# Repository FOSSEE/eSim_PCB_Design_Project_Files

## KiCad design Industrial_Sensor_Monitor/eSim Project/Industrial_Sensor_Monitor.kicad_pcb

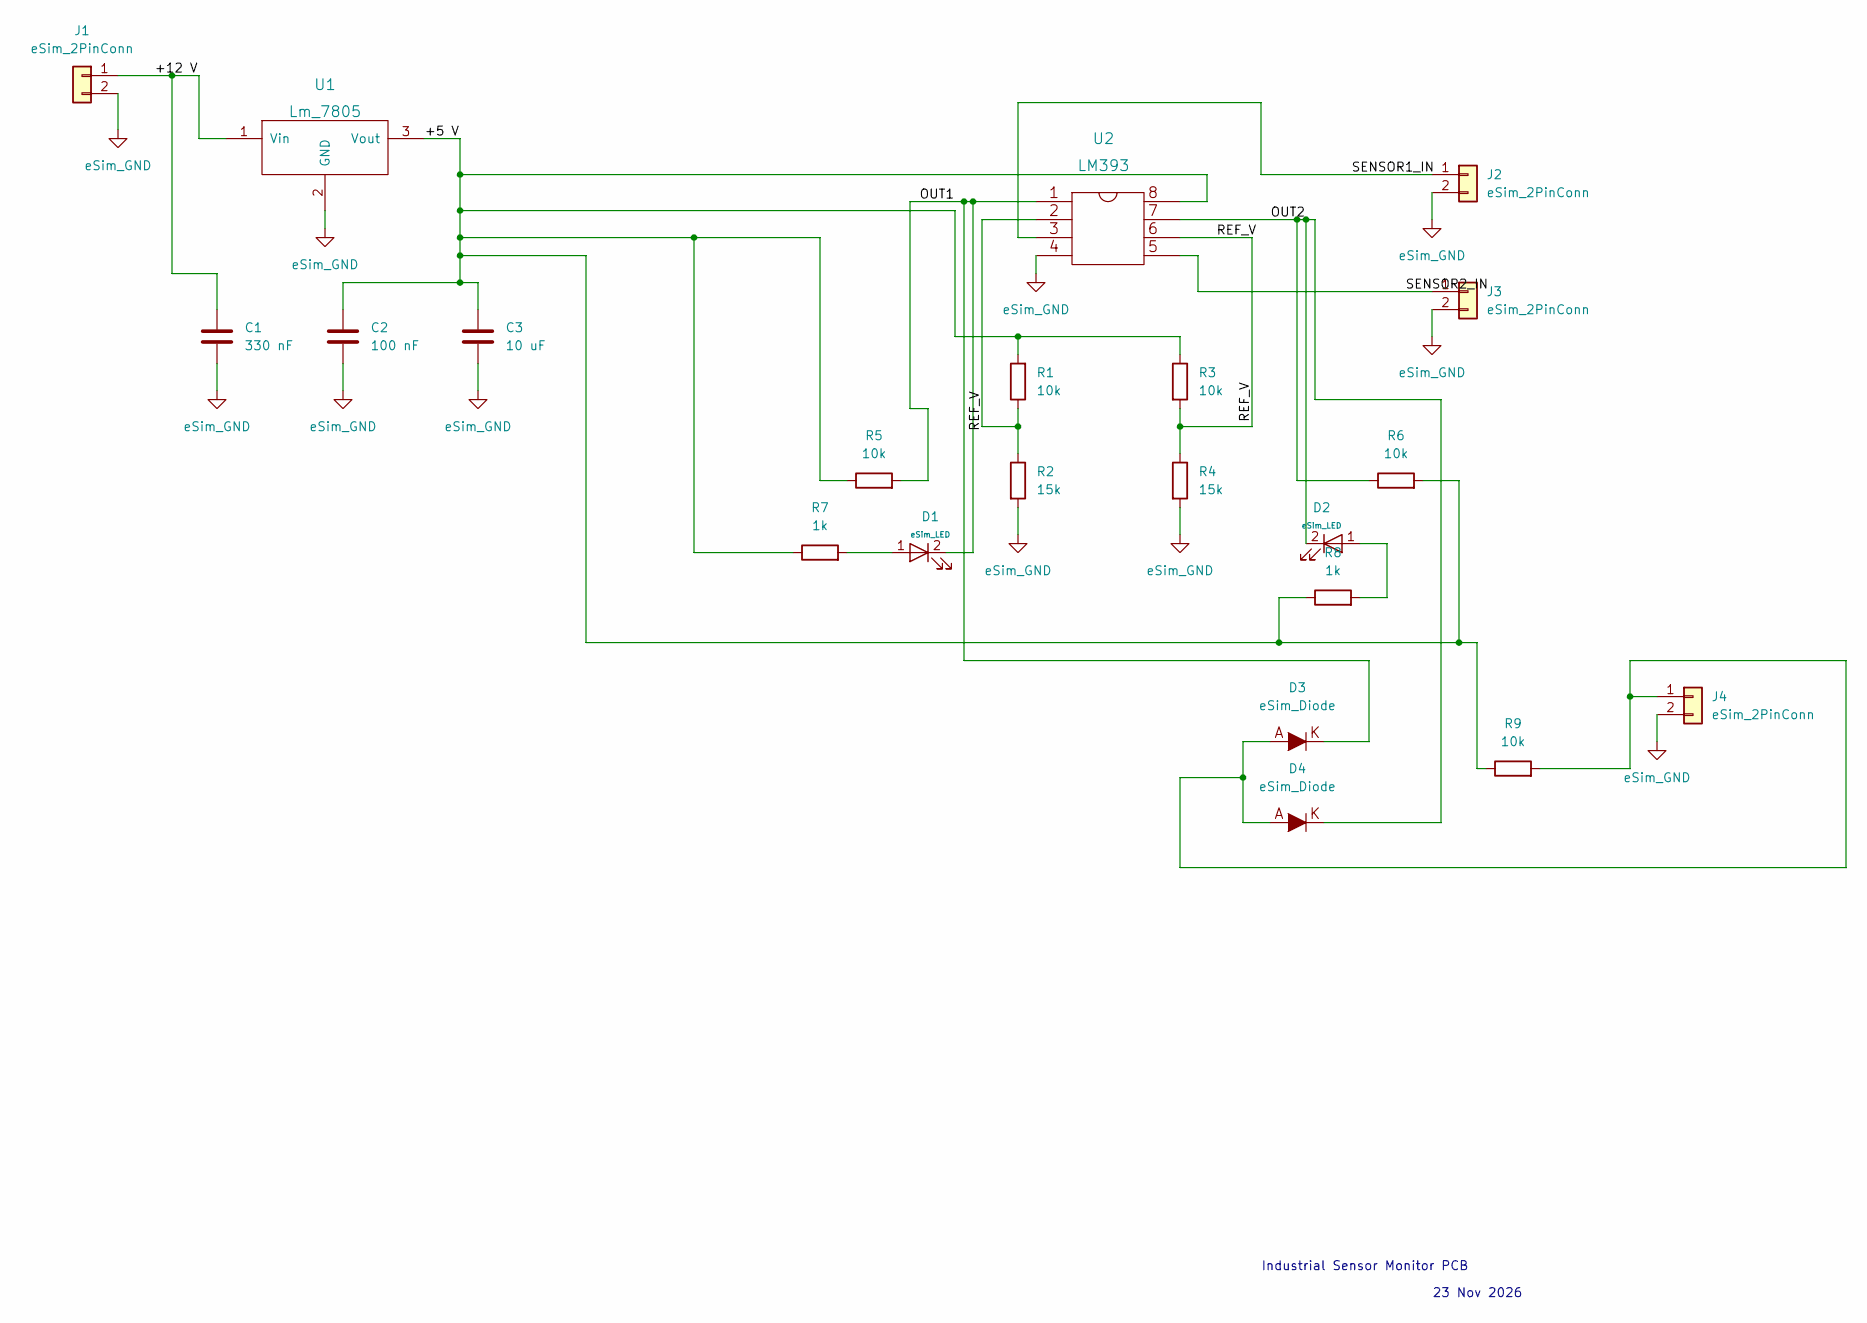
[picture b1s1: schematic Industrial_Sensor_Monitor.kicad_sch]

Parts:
C1: 330 nF; C_Disc_D5.0mm_W2.5mm_P2.50mm
C2: 100 nF; C_Disc_D5.0mm_W2.5mm_P2.50mm
C3: 10 uF; CP_Radial_D6.3mm_P2.50mm
D1, D2: eSim_LED; LED_D5.0mm
D3, D4: eSim_Diode; D_DO-35_SOD27_P7.62mm_Horizontal
J1, J2, J3, J4: eSim_2PinConn; TerminalBlock_Phoenix_MKDS-1,5-2-5.08_1x02_P5.08mm_Horizont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
R1, R3, R5, R6, R9: 10k; R_Axial_DIN0207_L6.3mm_D2.5mm_P7.62mm_Horizontal
R2, R4: 15k; R_Axial_DIN0207_L6.3mm_D2.5mm_P7.62mm_Horizontal
R7, R8: 1k; R_Axial_DIN0207_L6.3mm_D2.5mm_P7.62mm_Horizontal
U1: Lm_7805; TO-220-3_Vertical
U2: LM393; DIP-8_W7.62mm

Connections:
/+5 V: C2.1, C3.1, R1.2, R3.1, R5.1, R6.2, R7.1, R8.1, R9.1, U1.3 (Vout), U2.1 (8)
/+12 V: C1.1, J1.1, U1.1 (Vin)
/OUT1: D1.2 (K), D3.2 (K), R5.2, U2.4 (1)
/OUT2: D2.2 (K), D4.2 (K), R6.1, U2.8 (7)
/REF_V: R1.1, R2.1, R3.2, R4.1, U2.3 (2), U2.7 (6)
/SENSOR1_IN: J2.1, U2.2 (3)
/SENSOR2_IN: J3.1, U2.6 (5)
GND: C1.2, C2.2, C3.2, J1.2, J2.2, J3.2, J4.2, R2.2, R4.2, U1.2 (GND), U2.5 (4)
unnamed: D1.1 (A), R7.2
unnamed: D2.1 (A), R8.2
unnamed: D3.1 (A), D4.1 (A), J4.1, R9.2

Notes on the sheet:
Industrial Sensor Monitor PCB
23 Nov 2026

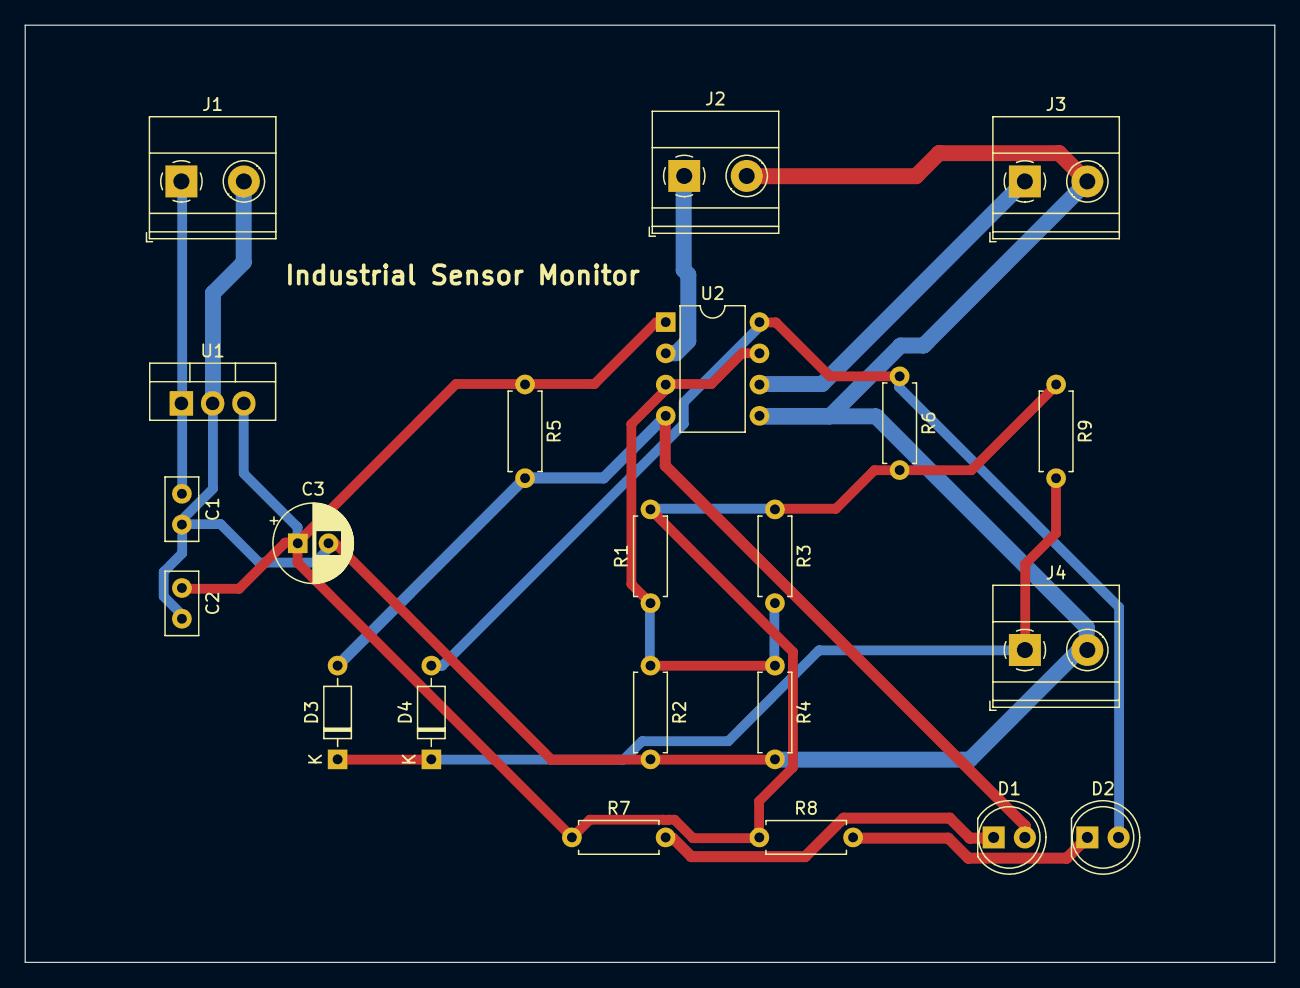
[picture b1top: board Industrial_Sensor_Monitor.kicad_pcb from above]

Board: 2 copper layers, 101.6 x 76.2 mm, 22 parts (0 on the bottom side), 11 nets.

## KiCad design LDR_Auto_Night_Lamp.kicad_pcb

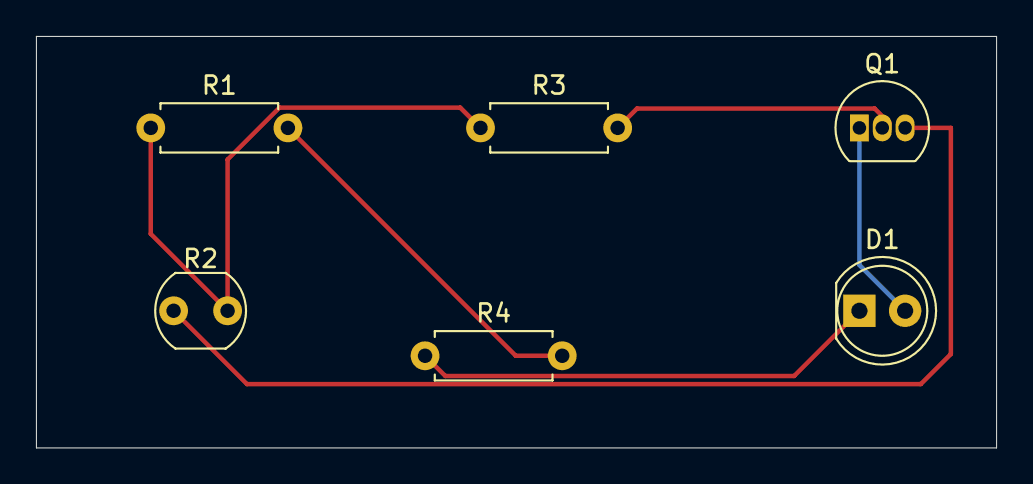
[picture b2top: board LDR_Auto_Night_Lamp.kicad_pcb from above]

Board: 2 copper layers, 53.3 x 22.9 mm, 6 parts (0 on the bottom side), 6 nets.

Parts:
D1: LED; LED_D5.0mm
Q1: BC547; TO-92_Inline
R1, R3: 10k; R_Axial_DIN0207_L6.3mm_D2.5mm_P7.62mm_Horizontal
R2: LDR (GL5528); R_LDR_5.0x4.1mm_P3mm_Vertical
R4: 330; R_Axial_DIN0207_L6.3mm_D2.5mm_P7.62mm_Horizontal

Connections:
GND: Q1.3 (E), R2.1
unnamed: D1.1 (+), R4.1
unnamed: D1.2 (-), Q1.1 (C)
unnamed: Q1.2 (B), R3.2
unnamed: R1.1, R2.2, R3.1
VCC: R1.2, R4.2

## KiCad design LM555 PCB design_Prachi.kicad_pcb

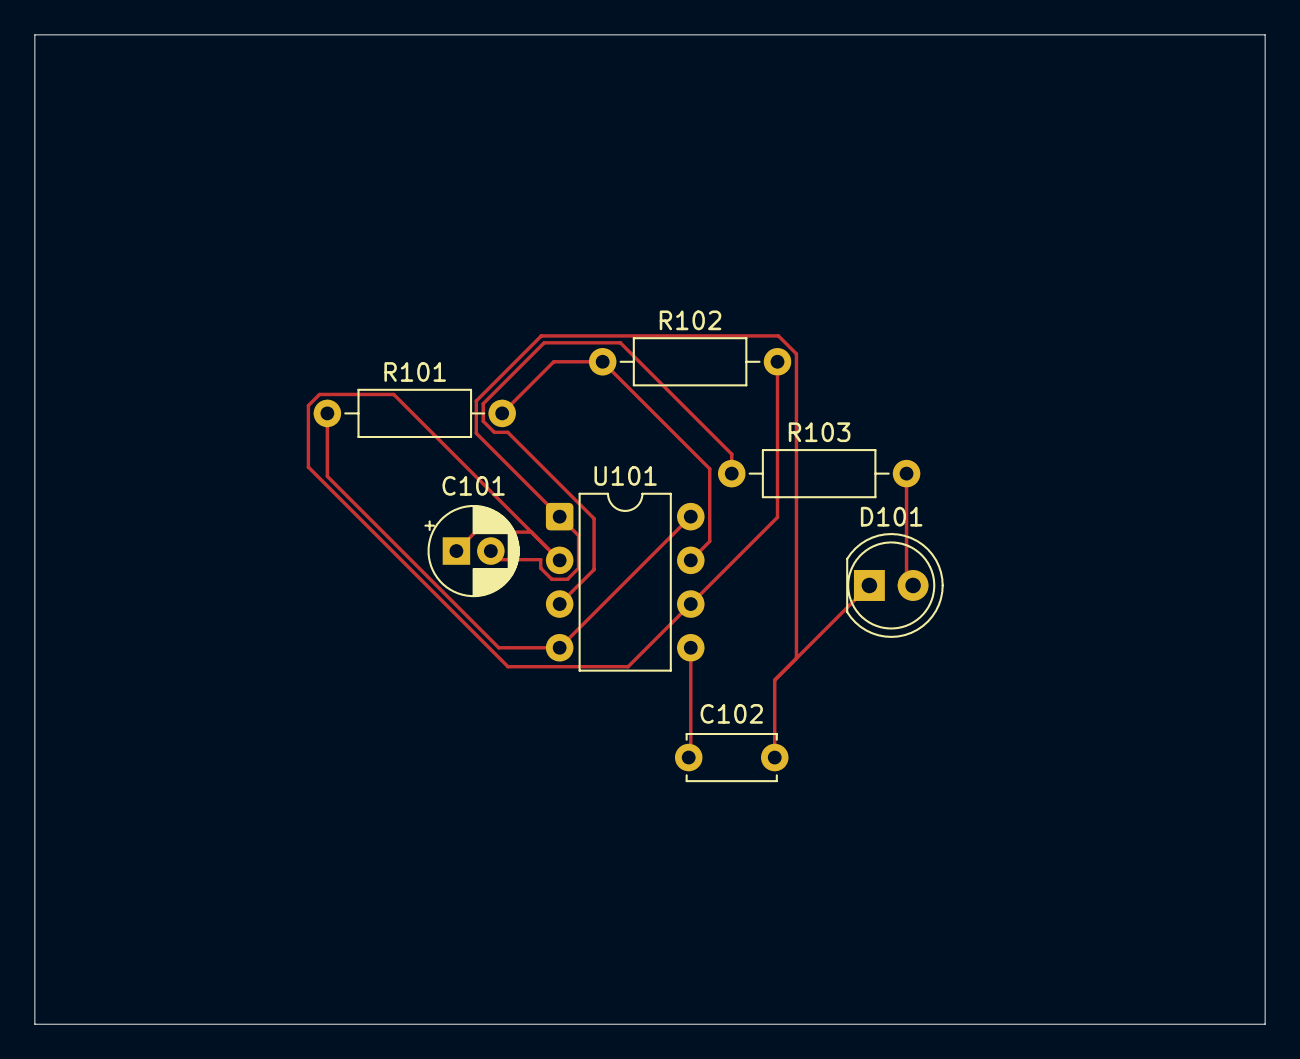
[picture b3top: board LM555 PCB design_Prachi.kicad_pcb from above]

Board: 2 copper layers, 71.5 x 57.5 mm, 7 parts (0 on the bottom side), 7 nets.

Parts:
C101: 10uF; CP_Radial_D5.0mm_P2.00mm
C102: 10nF; C_Disc_D5.0mm_W2.5mm_P5.00mm
D101: LED; LED_D5.0mm
R101: 1k; R_Axial_DIN0207_L6.3mm_D2.5mm_P10.16mm_Horizontal
R102: 47k; R_Axial_DIN0207_L6.3mm_D2.5mm_P10.16mm_Horizontal
R103: 330; R_Axial_DIN0207_L6.3mm_D2.5mm_P10.16mm_Horizontal
U101: LM555xN; DIP-8_W7.62mm

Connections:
GND: C101.2, C102.2, D101.1 (K), U101.1 (GND)
unnamed: D101.2 (A), R103.2
unnamed: C102.1, U101.5 (CV)
unnamed: R101.2, R102.1, U101.7 (DIS)
unnamed: R103.1, U101.3 (Q)
unnamed: R101.1, U101.4 (R), U101.8 (VCC)
unnamed: C101.1, R102.2, U101.2 (TR), U101.6 (THR)

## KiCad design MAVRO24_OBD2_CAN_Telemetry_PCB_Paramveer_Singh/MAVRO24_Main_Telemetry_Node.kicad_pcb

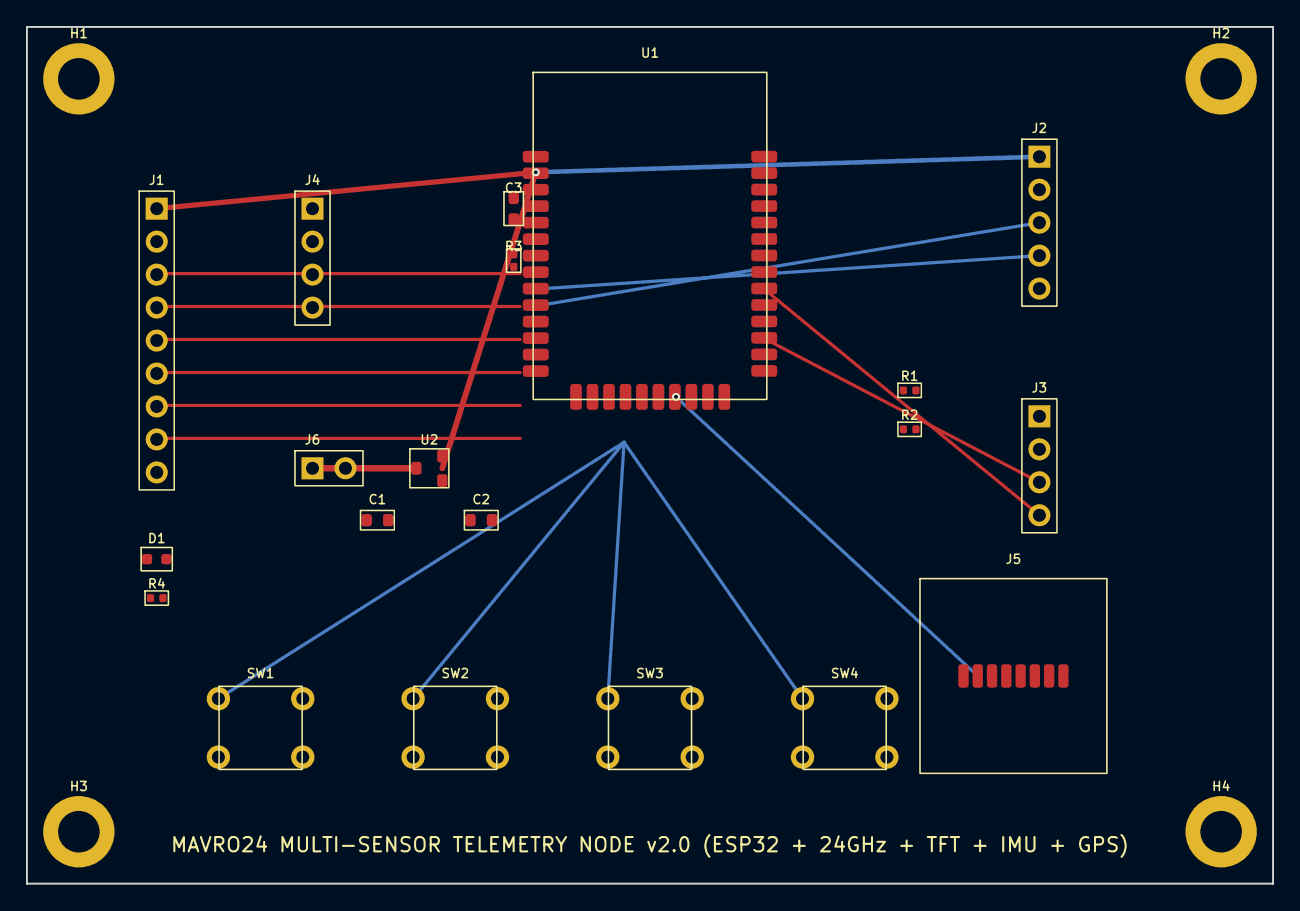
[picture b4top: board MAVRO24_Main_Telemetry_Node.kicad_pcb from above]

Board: 2 copper layers, 96.0 x 66.0 mm, 24 parts (0 on the bottom side), 22 nets.

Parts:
C1: 10uF_5V; C_0603_1608Metric
C2: 10uF_3V3; C_0603_1608Metric
C3: 100nF_ESP; C_0603_1608Metric
D1: PWR_3V3_GRN; LED_0603_1608Metric
H1, H2, H3, H4: M3; MountingHole_3.2mm_M3
J1: ILI9341_SPI_TFT; PinHeader_1x09_P2.54mm_Vertical
J2: HMMD_24GHz_3V3_ONLY; PinHeader_1x05_P2.54mm_Vertical
J3: MPU6050_I2C_0x68; PinHeader_1x04_P2.54mm_Vertical
J4: NEO6M_GPS_UART1; PinHeader_1x04_P2.54mm_Vertical
J5: MICROSD_BLACKBOX; microSD_HC_Hirose_DM3AT-SF-PEJM5
J6: PWR_5V_IN; PinHeader_1x02_P2.54mm_Vertical
R1: 4.7k_SCL; R_0402_1005Metric
R2: 4.7k_SDA; R_0402_1005Metric
R3: 10k_EN; R_0402_1005Metric
R4: 1k_LED; R_0402_1005Metric
SW1: PREV_D13; SW_PUSH_6mm
SW2: SEL_D14; SW_PUSH_6mm
SW3: NEXT_D32; SW_PUSH_6mm
SW4: AUTO_D17; SW_PUSH_6mm
U1: ESP32-WROOM-32
U2: LDO_3V3_REG; SOT-23

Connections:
BTN_AUTO: SW4.1, SW4.2, U1.24
BTN_NEXT: SW3.1, SW3.2, U1.35
BTN_PREV: SW1.1, SW1.2, U1.13
BTN_SEL: SW2.1, SW2.2, U1.12
EN: R3.1, U1.3
GND: C1.2, C2.2, C3.2, D1.2, H1.1, H2.1, H3.1, H4.1, J1.2, J2.2, J3.2, J4.2, J5.6, J6.2, R4.2, SW1.3, SW1.4, SW2.3, SW2.4, SW3.3, SW3.4, SW4.3, SW4.4, U1.1, U1.14, U1.25, U1.38, U2.2
GPS_RX: J4.4, U1.9
GPS_TX: J4.3, U1.36
I2C_SCL: J3.3, R1.1, U1.27
I2C_SDA: J3.4, R2.1, U1.30
RADAR_OT2: J2.5, U1.4
RADAR_RX: J2.4, U1.10
RADAR_TX: J2.3, U1.11
SD_CS: J5.2, U1.21
TFT_CS: J1.3, U1.33
TFT_DC: J1.5, U1.22
TFT_MISO: J1.9, J5.7, U1.31
TFT_MOSI: J1.6, J5.3, U1.26
TFT_RST: J1.4, U1.34
TFT_SCK: J1.7, J5.5, U1.32
VCC_3V3: C2.1, C3.1, D1.1, J1.1, J1.8, J2.1, J3.1, J5.4, R1.2, R2.2, R3.2, R4.1, U1.2, U2.3
VCC_5V: C1.1, J4.1, J6.1, U2.1

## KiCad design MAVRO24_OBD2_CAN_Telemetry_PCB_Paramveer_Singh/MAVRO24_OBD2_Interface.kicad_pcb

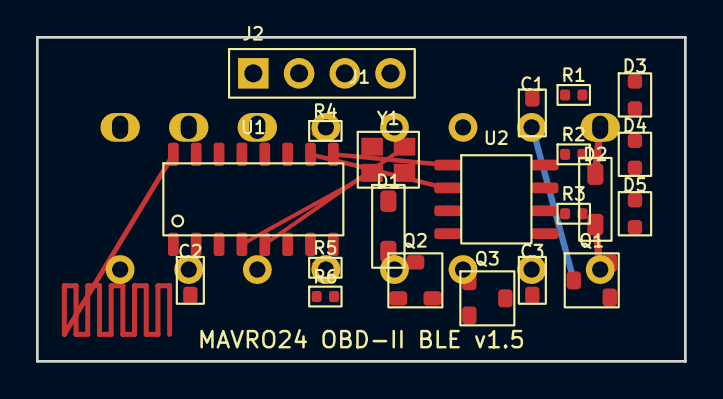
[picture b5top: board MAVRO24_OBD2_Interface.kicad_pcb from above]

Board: 2 copper layers, 36.0 x 18.0 mm, 22 parts (0 on the bottom side), 15 nets.

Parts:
C1: 10uF_3V3; C_0603_1608Metric
C2: 100nF_MCU; C_0603_1608Metric
C3: 100nF_VBAT; C_0603_1608Metric
D1: 1N4148_CLAMP; D_SOD-123
D2: SS14_SCHOTTKY; D_SOD-123
D3: PWR_RED; LED_0603_1608Metric
D4: BLE_BLU; LED_0603_1608Metric
D5: OBD_GRN; LED_0603_1608Metric
J1: OBD2_J1962_PLUG; OBD2_J1962_16pin_Plug_Pads
J2: UART_DBG; PinHeader_1x04_P2.54mm_Vertical
Q1: AMS1117-3.3_SOT23; SOT-23
Q2: MMBT3904_K_LINE; SOT-23
Q3: MMBT3904_L_LINE; SOT-23
R1, R2, R3, R4, R5, R6: 120R/10k; R_0402_1005Metric
U1: ELM327_BLE_MCU; SOIC-16_3.9x9.9mm_P1.27mm
U2: LM393_DR; SOIC-8_3.9x4.9mm_P1.27mm
Y1: 24.000MHz; Crystal_SMD_2520-4Pin_2.5x2.0mm

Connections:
CAN_H: D1.1, J1.6, R4.1, U1.13
CAN_L: J1.14, R4.2, U1.12
GND: C1.2, C2.2, C3.2, D1.2, J2.4, Q1.1, Q2.2, Q3.2, R1.2, R2.2, R3.2, U1.2, U1.9, U2.4, Y1.2, Y1.4
K_LINE: J1.7, Q2.1, R5.1, U1.11, U2.1, U2.2, U2.3
LED_PWR: D3.2, R1.1
LED_RX: D5.2, R3.1, U1.8
LED_TX: D4.2, R2.1, U1.7
L_LINE: J1.15, Q3.1, R6.1, U1.10, U2.5, U2.6, U2.7
UART_RX: J2.3, Q3.3, U1.6
UART_TX: J2.2, Q2.3, U1.5
VBAT_12V: D2.1, J1.16
VBAT_PROT: C3.1, D2.2, Q1.2, U2.8
VCC_3V3: C1.1, C2.1, D3.1, D4.1, D5.1, J2.1, Q1.3, R5.2, R6.2, U1.1
XTAL_A: U1.3, Y1.1
XTAL_B: U1.4, Y1.3

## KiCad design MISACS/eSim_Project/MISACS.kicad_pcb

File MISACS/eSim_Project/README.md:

# Modular Industrial Sensor Acquisition and Control System (MISACS)
## FOSSEE eSim Winter Internship 2026 — Task 7 Master Release Candidate (Phase 3 Final Review Candidate)

**Project Title:** Modular Industrial Sensor Acquisition and Control System (MISACS)  
**EDA Suite:** eSim 2.5 (FOSSEE, IIT Bombay) + KiCad 6.0.11  
**Target Hardware:** Industrial Mixed-Signal Edge Controller  
**Release Date:** November 2026  
**Revision:** Phase 3 Final Review Candidate  
**Status:** Engineering Release Candidate — Pending Physical Prototype Validation  

---

## 1. Project Directory Structure

```text
eSim_Project/
├── MISACS.proj                 # Canonical eSim 2.5 Project Anchor (schematicFile MISACS.kicad_sch)
├── MISACS.kicad_sch            # Canonical Schematic (0 Native ERC Errors, 74 lib_symbol_issues warnings)
├── MISACS.kicad_pcb            # Canonical 2-Layer PCB (0 DRC Violations, 0 Unconnected Pads)
├── MISACS.kicad_pro            # KiCad 6 Project Settings & Design Rules
├── sym-lib-table               # Local Symbol Library Table
├── fp-lib-table                # Local Footprint Library Table
├── README.md                   # Master project README and instruction guide
├── run_simulations.py          # Portable, Non-Destructive 10-Testbench Hardened Simulation Runner
├── MISACS_PHASE3_RELEASE_MANIFEST_SHA256.txt # Cryptographic SHA-256 release manifest
├── BOM/                        # Bill of Materials
│   ├── MISACS_BOM.csv          # Structured CSV BOM (70 Circuit Components + 4 Mounting Holes)
│   └── MISACS_BOM.md           # Formatted Markdown BOM with MPNs, Footprints, and Sourcing
├── Gerber/                     # Manufacturing RS-274X Gerbers and Excellon Drill Files
│   ├── MISACS-F_Cu.gbr         # Top Copper Layer
│   ├── MISACS-B_Cu.gbr         # Bottom Copper Layer & Solid GND Plane
│   ├── MISACS-F_Mask.gbr       # Top Solder Mask
│   ├── MISACS-B_Mask.gbr       # Bottom Solder Mask
│   ├── MISACS-F_SilkS.gbr      # Top Silkscreen Legend
│   ├── MISACS-B_SilkS.gbr      # Bottom Silkscreen
│   ├── MISACS-F_Paste.gbr      # Top Solder Paste (Stencil)
│   ├── MISACS-B_Paste.gbr      # Bottom Solder Paste
│   ├── MISACS-Edge_Cuts.gbr    # Board Outline (100.00 mm x 80.00 mm nom. centerline, 100.15 x 80.15 mm stroke)
│   ├── MISACS-PTH.drl          # Plated Through-Hole Drill File
│   └── MISACS-NPTH.drl         # Non-Plated Through-Hole Drill File (M3 Mounting Holes)
├── Reports/                    # Official Engineering Audit Reports
│   ├── PHASE3_6_BASELINE_MANIFEST.txt
│   ├── MISACS_PHASE3_6_ERC.rpt # Native KiCad 6.0.11 ERC Report (0 Errors, 74 Warnings)
│   ├── MISACS_PHASE3_6_DRC.rpt # Native KiCad 6.0.11 DRC Report (0 Violations, 0 Unconnected)
│   ├── SCHEMATIC_PCB_NETLIST_PARITY_REPORT.txt # 192 Connected + 4 NC Endpoints = 196 Total
│   ├── MECHANICAL_MANUFACTURING_REPORT.txt
│   ├── GERBER_DRILL_MANIFEST.txt
│   ├── FINAL_AUDIT_VERIFICATION_TABLE.md
│   └── MISACS_PHASE3_RELEASE_MANIFEST_SHA256.txt
├── Simulation/                 # 10 Functional Ngspice Testbenches & Netlists
│   ├── SIMULATION_REPORT.md    # Complete Simulation Verification Document
│   ├── SIMULATION_RUN_MANIFEST.json # Automated execution tracking and cryptographic manifest
│   ├── run_simulations.py      # Hardened simulation runner (synchronized copy)
│   ├── tb1_input_protection.cir & tb1_plot.svg (24V TVS Clamp & D14 Reverse Shunt Diode)
│   ├── tb2_lm2576_buck.cir & tb2_plot.svg (24V -> 5V Buck Regulator 52kHz)
│   ├── tb3_ams1117.cir & tb3_plot.svg (5V -> 3.3V LDO Series Distributed Ceramic Network)
│   ├── tb4_current_loop.cir & tb4_plot.svg (4-20mA 100R Shunt & Buffer)
│   ├── tb5_voltage_input.cir & tb5_plot.svg (0-10V 4:1 Divider & Buffer)
│   ├── tb6_adc_protection.cir & tb6_plot.svg (ADS1115 BAT54S Rail Clamp)
│   ├── tb7_gate_drive.cir & tb7_plot.svg (UCC27524 Gate Driver & NMOS)
│   ├── tb8_dual_actuators.cir & tb8_plot.svg (Dual Actuators 4A / 2.5A)
│   ├── tb9_flyback_clamp.cir & tb9_plot.svg (10mH Inductive Flyback Clamp)
│   └── tb10_rs485_bus.cir & tb10_plot.svg (RS-485 Differential Bus Signaling)
├── Negative_Testing/           # Automated Verification of Runner Error Traps
│   ├── README.md               # Negative testing documentation and execution guide
│   ├── test_negative_cases.py  # Standalone suite verifying 9 error trapping cases
│   └── NEGATIVE_TEST_REPORT.json # Sanitized machine-readable negative test report
├── Documentation/              # 13 Exhaustive Technical Engineering Documents
│   ├── 01_PROJECT_OVERVIEW_ARCHITECTURE.md
│   ├── 02_FUNCTIONAL_BLOCK_DIAGRAM.md
│   ├── 03_SCHEMATIC_DOCUMENTATION.md
│   ├── 04_PCB_LAYER_ROUTING_EXPLANATION.md
│   ├── 05_POWER_PROTECTION_CALCULATIONS.md
│   ├── 06_ANALOG_INPUT_CALCULATIONS.md
│   ├── 07_THERMAL_CURRENT_CARRYING_ANALYSIS.md
│   ├── 08_SIMULATION_METHODOLOGY_RESULTS.md
│   ├── 09_ERC_REPORT.md
│   ├── 10_DRC_REPORT.md
│   ├── 11_GERBER_EXCELLON_VALIDATION.md
│   ├── 12_KNOWN_LIMITATIONS_ASSUMPTIONS.md
│   ├── 13_ASSEMBLY_CONNECTOR_PINOUT.md
│   └── FINAL_AUDIT_VERIFICATION_TABLE.md
└── Evidence/                   # Visual Verification Artifacts, Logs & Vector Renders
    ├── Simulation_Logs/        # Persistent Execution Logs for TB1-TB10
    │   ├── TB1_execution.log through TB10_execution.log
    ├── MISACS-MISACS_PCB_Board_Outline_Edge_Cuts.svg
    ├── MISACS-MISACS_PCB_Bottom_Layer_B_Cu.svg
    ├── MISACS-MISACS_PCB_Bottom_Silkscreen_B_SilkS.svg
    ├── MISACS-MISACS_PCB_Top_Layer_F_Cu.svg
    ├── MISACS-MISACS_PCB_Top_Silkscreen_F_SilkS.svg
    ├── MISACS-MISACS_PCB_Top_Solder_Mask_F_Mask.svg
    ├── MISACS_NATIVE_ERC_RESULTS.txt
    ├── MISACS_NATIVE_DRC_RESULTS.txt
    ├── SCHEMATIC_PCB_PARITY_RESULTS.txt
    ├── MECHANICAL_MANUFACTURING_RESULTS.txt
    ├── GERBER_DRILL_MANIFEST.txt
    ├── FINAL_PROJECT_DIRECTORY_LISTING.txt
    └── tb1_plot.svg through tb10_plot.svg
```

---

## 2. Key Engineering Specifications & Reconciled Boundaries

1. **Power Supply & Protection:**
   - **Main 24V Input (J1):** Protected by Littelfuse SMBJ30A unidirectional TVS ($V_{RWM} = 30.0\,\text{V}, V_{BR} = 34.5\,\text{V}$, simulated clamp $44.020\,\text{V} < 60.0\,\text{V}$), series Schottky diode D2 (SS36) on logic rail ($V_{prot} = -0.0000\,\text{V}$), and shunt Schottky diode D14 (SS56) across J1 entry terminals as a reverse-polarity shunt diode (clamped to $-1.432\,\text{V}$ under a static DC sweep with $0.5\,\Omega$ source resistance; $-0.75\,\text{V}$ static $V_F$ at 5A).
   - **Mandatory Installation & Fuse Coordination Notice:**
     - D14 non-repetitive surge rating is $I_{FSM} = 150\,\text{A}$ ($8.3\,\text{ms}$ single half-sine wave, energy integral $I^2t \approx 93.38\,\text{A}^2\text{s}$). Under sustained reverse connection from an uncoordinated source (such as a 5A current-limited bench supply), D14 dissipates $>3.75\,\text{W}$ continuously and will suffer thermal destruction within seconds.
     - Upstream protection requires careful fuse selection. Manufacturer datasheet ratings for candidate 5A Littelfuse parts show significant differences:
       * **0451005.MRL (SMT 2410 fast-acting):** DC interrupting rating of **300A @ 32VDC**; nominal melting $I^2t = 5.566\,\text{A}^2\text{s}$; total clearing $I^2t$ unpublished.
       * **0217005.MXP ($5\times 20\,\text{mm}$ glass):** AC rating 50A @ 250VAC, but DC interrupting rating is limited to **70A @ 60VDC**; melting $I^2t = 42.795\,\text{A}^2\text{s}$; total clearing $I^2t$ unpublished. If prospective DC fault current exceeds 70A, this fuse cannot safely extinguish the arc.
       * **0216005.MXP ($5\times 20\,\text{mm}$ ceramic):** AC rating 1500A @ 250VAC; **NO DC interrupting rating published** (an AC breaking rating cannot be applied to DC circuits).
     - The nominal fuse melting $I^2t$ is lower than the calculated diode non-repetitive surge $I^2t$ equivalent ($5.566\,\text{A}^2\text{s} < 93.38\,\text{A}^2\text{s}$), but this comparison does not establish protection coordination or prove diode survival. Maximum total-clearing $I^2t$ remains unpublished, and actual fault conditions are installation-dependent. Manufacturer time-current curves reflect pre-arcing opening time only, not guaranteed total-clearing time. Prospective clearing current cannot be claimed as "1–5 ms" without a verified source model. Generic arcing multipliers and foldback assumptions are formally retracted.
     - D14 Reverse Shunt Diode Status: **CONDITIONAL / NOT VERIFIED** (requires physical prototype qualification and strict source coordination).
   - **5V Buck Converter:** LM2576HVS-5.0 with Bourns SRR1260-101M ($100\,\mu\text{H}$, $1.70\,\text{A} I_{rms} / 1.70\,\text{A} I_{sat}$, worst-case DCR $R_{L1} = 0.18\,\Omega$, $\Delta I_L = 1.092\,\text{A}$). Sized for **1.15A continuous worst-case (1.32A nominal continuous)**, providing a $3.83\times$ safety margin over actual onboard system demand ($0.298\,\text{A} \approx 0.30\,\text{A}$). Qualified simulation (TB2) with worst-case $0.18\,\Omega$ DCR yields steady-state mean of $4.993\,\text{V}$ and ripple of $67.59\,\text{mV}_{p-p}$ ($1.5-2.0\,\text{ms}$).
   - **3.3V Linear Regulator:** AMS1117-3.3 delivering $285.3\,\text{mA}$ peak ($0.485\,\text{W}$ load, $0.025\,\text{W}$ quiescent, $0.510\,\text{W}$ total), operating with an estimated $T_j = 83.15^\circ\text{C}$ at $50^\circ\text{C}$ ambient ($41.85^\circ\text{C}$ margin below $125^\circ\text{C}$). TB3 verifies physical series trace parasitics ($18\,\text{m}\Omega, 16\,\text{nH}$), producing an exact DC trace drop of $\mathbf{5.14\,\text{mV}}$ ($5.135\,\text{mV}$). Stability status: **Plausible under static conditions, but unverified and potentially marginal under dynamic Wi-Fi pulsed loads — awaiting physical prototype testing; hardware correction option identified** (C10 pads accommodate hand-soldering of EIA Case A tantalum capacitor for bench validation).

2. **Analog Front Ends:**
   - **4–20 mA Current Loop:** Susumu $100.0\,\Omega$ ($0.1\%$, $25\,\text{ppm}$) precision shunt, TI TPS26610DDFR active eFuse loop limiter (SOT-23-THIN / DDF-8, footprint SOT-23-8), and TI LMV358 buffer ($0.400\,\text{V}$ to $2.000\,\text{V}$). Pin 7 (VSNS) and Pin 8 (SGOOD) intentionally unconnected (NC). TB4 confirms linear regression $R^2_{reg} = 1.000000$ (slope $100.000\,\text{V/A}$, intercept $0.0000\,\text{V}$) and ideal transfer agreement $R^2_{ideal} = 1.000000$ (with $SS_{ideal\_tot} = \sum (V_{ideal,i} - \bar{V}_{ideal})^2$).
   - **0–10 V Voltage Input:** Precision $4:1$ divider ($30.0\,\text{k}\Omega / 10.0\,\text{k}\Omega$, $0.1\%$) and TI LMV358 buffer ($0.000\,\text{V}$ to $2.500\,\text{V}$). TB5 verifies exact 4.000:1 division across $0-10\,\text{V}$ and over-range safety at $12.0\,\text{V}$ ($3.0000\,\text{V} \le 3.3\,\text{V}$).
   - **ADC Protection (TB6):** Diodes Inc. BAT54S dual Schottky rail clamps and TI ADS1115 16-bit delta-sigma ADC. Pin 2 (ALERT/RDY) intentionally NC.
     * **Simulation Execution Status:** **PASS** (Nominal room-temperature clamp $-0.281\,\text{V}$ and $+3.591\,\text{V}$ satisfy nominal boundary limits).
     * **Engineering Qualification Status:** **CONDITIONAL / NOT VERIFIED**.
     * **Engineering Rationale:**
       1. At cold ambient temperatures (e.g. $-40^\circ\text{C}$), BAT54S forward voltage rises to $\approx 0.45\,\text{V}$ (typical curve reading, as guaranteed limits are specified only at $25^\circ\text{C}$). This exceeds the ADS1115 absolute maximum rating ($\text{GND}-0.30\,\text{V}$ / $V_{DD}+0.30\,\text{V}$), resulting in negative voltage margin and forcing internal ESD protection diodes to conduct.
       2. During a $+10\,\text{V}$ overvoltage fault, $6.41\,\text{mA}$ is injected into the $+3.3\,\text{V}$ rail through the upper clamp. The AMS1117 linear regulator cannot sink current. When the MCU is operating in active mode ($80-240\,\text{mA}$), this current is safely absorbed. However, if the MCU enters deep sleep ($<100\,\mu\text{A}$), the injected current charges the rail capacitance ($16\,\mu\text{F}$) with a first-order initial slope estimate of $dV/dt \approx 405\,\text{V/s}$ (analytical estimate, not a transient simulation or destruction guarantee; dynamic model and bench validation required).
     * **Hardware Correction Evaluation:** Generic clamp diodes are unviable: MMSZ5227B is not guaranteed to remain below the 3.60 V maximum at its upper tolerance limit (3.78 V), SMAJ3.3A does not conduct at 3.60 V (breakdown 4.10–4.70 V), and no evaluated candidate has been qualified as a suitable solution. The proposed 4.7 kΩ R7 option remains a proposed future hardware change (not an implemented PCB modification), and any revised protection network requires additional electrical analysis and physical testing.

3. **Digital Core & Industrial Communication:**
   - **MCU:** Espressif ESP32-WROOM-32E-N16 (240 MHz dual-core, 16MB SPI Flash). Pin 14 (IO12 / MTDI) intentionally NC to ensure standard 3.3V flash boot.
   - **RS-485 Transceiver:** Maxim / ADI MAX3485EESA half-duplex transceiver. **Non-isolated design referenced to system ground.** Includes switchable $120\,\Omega$ bus termination, $390\,\Omega$ failsafe bias network, and Littelfuse SM712 asymmetrical TVS diode. TB10 confirms $2.10\,\text{V}_{pp}$ differential swing (mark $+1.150\,\text{V}$, space $-0.951\,\text{V}$).

4. **Dual Power Actuator Drivers:**
   - **Driver & Switches:** TI UCC27524 high-speed dual gate driver driving two Infineon IPD50N06S4L-08 $60\,\text{V}, 50\,\text{A}$ power MOSFETs in PG-TO252-3 package (KiCad footprint `TO-252-2`) with Vishay SS56 flyback clamp diodes (D8, D10). PCB features $42.90\,\text{mm}^2$ drain pads with **4 dedicated thermal stitching vias** ($0.40\,\text{mm}$ drill, $0.80\,\text{mm}$ annular ring) and $139.13\,\text{mm}^2$ total connected copper per channel.
   - **Thermal Matrix Formulation ($\theta_{11} = 52.0\,\text{K/W}, \theta_{12} = 6.5\,\text{K/W}$, $T_{amb} \le 50^\circ\text{C}$):**
     - Single Channel Continuous: Up to **4.0A continuous** ($T_j \approx 71.7^\circ\text{C}$ nominal, $\le 72.9^\circ\text{C}$ upper bound).
     - Dual Channels Simultaneously Active: **3.0A continuous per channel** ($6.0\,\text{A}$ combined, $T_j \approx 64.4^\circ\text{C}$ nominal, $\le 65.4^\circ\text{C}$ upper bound), or asymmetrical (e.g. 4.0A CH1 / 2.0A CH2, $T_{j1} \approx 72.4^\circ\text{C}$).
     - Pulsed Operation: **5.0A per channel at up to 50% PWM duty cycle** ($< 10\,\text{s}$ duration, $T_j \approx 68.5^\circ\text{C}$).
     - Forced-Air Cooling ($> 1\,\text{m/s}$): Up to **5.0A continuous per channel** ($T_j \approx 67.4^\circ\text{C}$, analytical upper bound $78.0^\circ\text{C}$).
     - Classification: **Estimated Design Envelopes — Pending Physical Thermal Qualification**.

5. **Physical Pin Endpoint Accounting:**
   - **192 Matched Connected Endpoints**
   - **4 Intentional No-Connect Endpoints** (U4.2 ALERT, U5.14 IO12, U8.7 VSNS, U8.8 SGOOD)
   - **196 Total Physical Component Pads / Nodes** across all 70 components
   - **0 Electrical Discrepancies**

---

## 3. How to Run Simulations
The simulation suite can be executed from the project root or the `Simulation/` directory:
```bash
python run_simulations.py
```
This performs:
- Automatic Ngspice binary location and environment hardening (Windows 8.3 short-path resolution, HOME trailing slash handling).
- Non-destructive execution in an isolated scratch directory without touching source `.cir` netlists.
- Strict tabular parsing rejecting malformed tokens, wrong column counts, and non-finite values (`NaN`, `Inf`).
- Mandatory measurement point validation across all 10 testbenches.
- Distinction between Simulation Execution Status (**PASS**) and Engineering Qualification Status (**CONDITIONAL / NOT VERIFIED** for TB6).
- Generation of standalone SVG plots, structured execution logs in `Evidence/Simulation_Logs/`, and cryptographic tracking in `Simulation/SIMULATION_RUN_MANIFEST.json`.

---

## 4. How to Run Automated Negative Testing
The automated error-trapping and boundary-enforcement negative testing suite can be executed from the project root or `Negative_Testing/`:
```bash
python Negative_Testing/test_negative_cases.py
```
This non-destructively verifies 9 controlled failure scenarios:
1. Insufficient TB4 regression sample count (2mA step generating exactly 9 operating interval samples, < 10 threshold).
2. Missing TB5 mandatory 12.0V over-range input check.
3. Malformed non-numeric token injection.
4. Non-finite token injection (`NaN` / `Inf`).
5. Missing simulator output data file.
6. Missing circuit SPICE netlist file.
7. Failed simulator executable invocation.
8. Universal report generation robustness without secondary crashes.
9. Deliberately perturbed TB4 ideal agreement dataset (+15mV offset producing $R^2_{ideal} = 0.999063 < 0.9999$ specific failure and helper unit testing).
Results are recorded in `Negative_Testing/NEGATIVE_TEST_REPORT.json`.

---

## 5. How to Open and Verify in eSim 2.5
1. Launch **eSim 2.5** graphical user interface.
2. Select **Project -> Open Project**.
3. In the directory browser dialog, navigate to the extracted release directory.
4. Select `MISACS.proj` (or select the project folder).
5. The eSim console and activity explorer will display:
   `Project MISACS opened successfully.`
6. Click the **Schematic Editor** (Eeschema) icon to open `MISACS.kicad_sch`. Confirm 0 errors on load.
7. Click the **PCB Editor** (Pcbnew) icon to open `MISACS.kicad_pcb`. Confirm board renders with complete routing and solid ground plane.

---

## 6. How to Open and Verify in KiCad 6.0.11
1. Open KiCad 6.0.11.
2. Select **File -> Open Project...** and choose `MISACS.kicad_pro`.
3. Open Schematic: Run **Inspect -> Electrical Rules Checker (ERC)** -> Confirm **0 Errors**, 74 documented `lib_symbol_issues` warnings (`Reports/MISACS_PHASE3_6_ERC.rpt`).
4. Open PCB Layout: Run **Inspect -> Design Rules Checker (DRC)** -> Confirm **0 Violations, 0 Unconnected Pads** (`Reports/MISACS_PHASE3_6_DRC.rpt`).

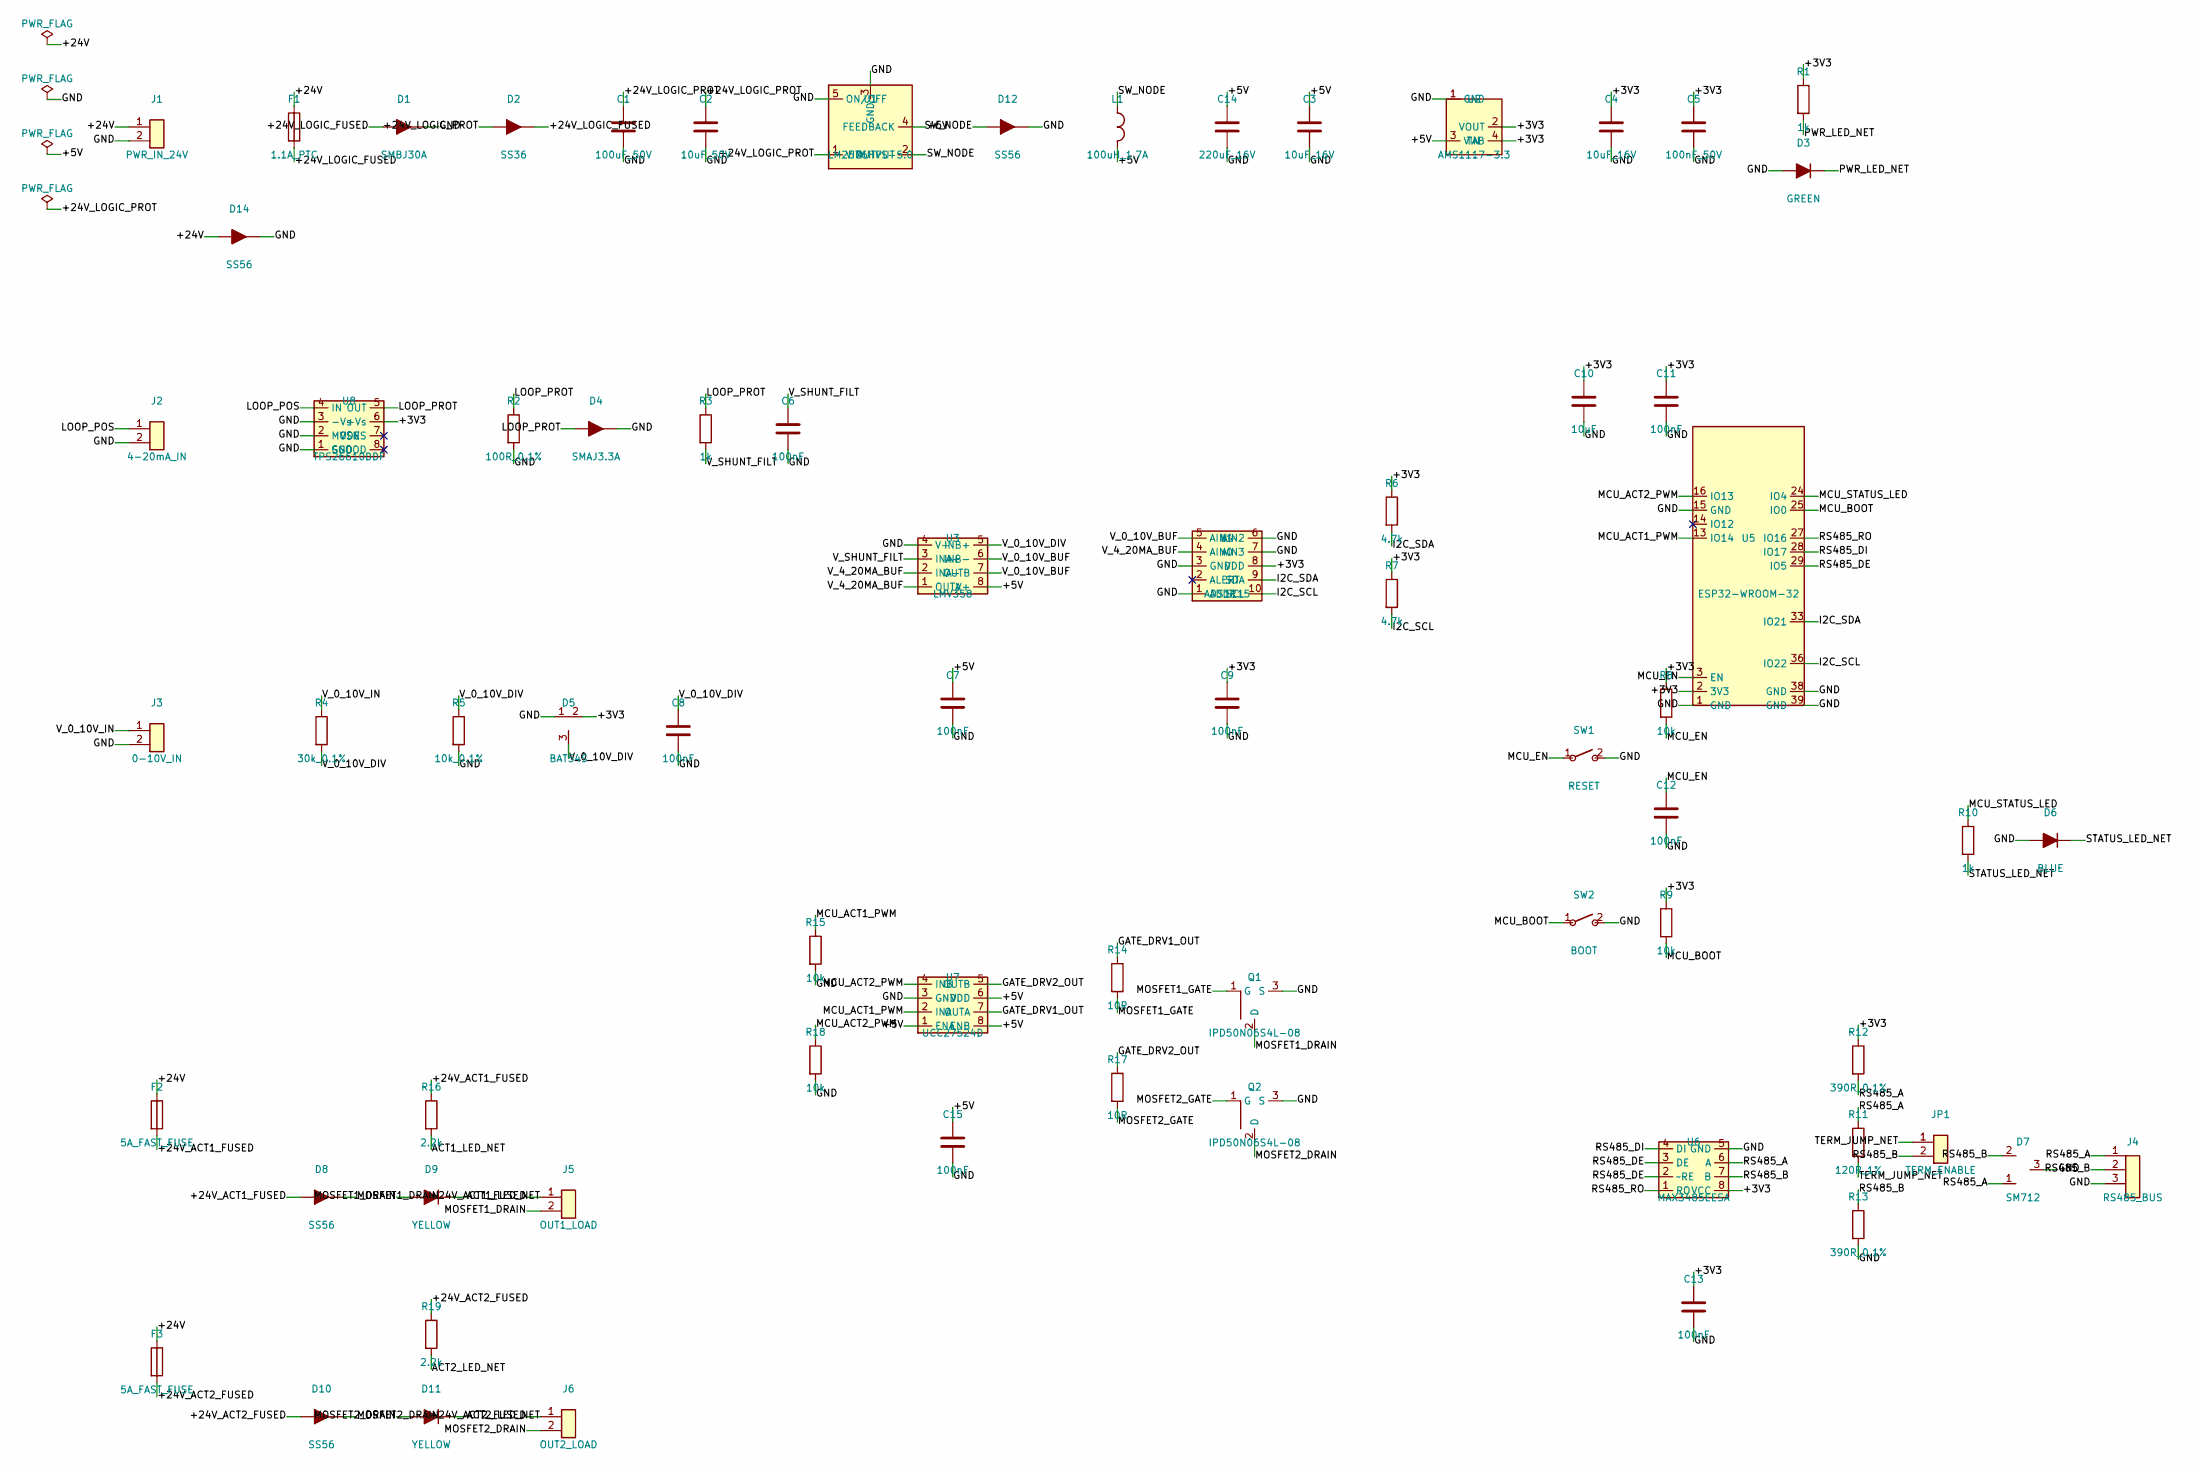
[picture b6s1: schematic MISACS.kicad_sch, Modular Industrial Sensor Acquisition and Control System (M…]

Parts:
C1: 100uF_50V; CP_Elec_8x10.5; MPN EEE-FK1H101P
C2: 10uF_50V; C_1206_3216Metric; MPN C1206C106K5RAC7800
C3, C4: 10uF_16V; C_0805_2012Metric; MPN GRM21BR71C106KE15L
C5: 100nF_50V; C_0805_2012Metric; MPN C0805C104K5RACTU
C6, C7, C8, C9, C11, C12, C13, C15: 100nF; C_0805_2012Metric; MPN C0805C104K5RACTU
C10: 10uF; C_1206_3216Metric; MPN C1206C106K5RAC7800
C14: 220uF_16V; CP_Elec_8x10.5; MPN EEE-FK1C221P
D1: SMBJ30A; D_SMB; MPN SMBJ30A
D2: SS36; D_SMC; MPN SS36-E3/57T
D3: GREEN; LED_0805_2012Metric; MPN LTST-C170KGKT
D4: SMAJ3.3A; D_SMA; MPN SMAJ3.3A
D5: BAT54S; SOT-23; MPN BAT54S-7-F
D6: BLUE; LED_0805_2012Metric; MPN LTST-C170TBKT
D7: SM712; SOT-23; MPN SM712-02HTG
D8, D10, D12, D14: SS56; D_SMC; MPN SS56-E3/57T
D9, D11: YELLOW; LED_0805_2012Metric; MPN LTST-C170KSKT
F1: 1.1A_PTC; Fuse_1812_4532Metric; MPN MF-MSMF110/33X-2
F2, F3: 5A_FAST_FUSE; Fuse_2410_6125Metric; MPN 0451005.MRL
J1: PWR_IN_24V; TerminalBlock_Phoenix_MKDS-1,5-2-5.08_1x02_P5.08mm_Horizont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; MPN 1715721
J2: 4-20mA_IN; TerminalBlock_Phoenix_MKDS-1,5-2-5.08_1x02_P5.08mm_Horizont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; MPN 1715721
J3: 0-10V_IN; TerminalBlock_Phoenix_MKDS-1,5-2-5.08_1x02_P5.08mm_Horizont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; MPN 1715721
J4: RS485_BUS; TerminalBlock_Phoenix_MKDS-1,5-3-5.08_1x03_P5.08mm_Horizont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; MPN 1715734
J5: OUT1_LOAD; TerminalBlock_Phoenix_MKDS-1,5-2-5.08_1x02_P5.08mm_Horizont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; MPN 1715721
J6: OUT2_LOAD; TerminalBlock_Phoenix_MKDS-1,5-2-5.08_1x02_P5.08mm_Horizont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; MPN 1715721
JP1: TERM_ENABLE; PinHeader_1x02_P2.54mm_Vertical; MPN 61300211121
L1: 100uH_1.7A; L_Bourns_SRR1260; MPN SRR1260-101M
Q1, Q2: IPD50N06S4L-08; TO-252-2; MPN IPD50N06S4L-08
R1, R3, R10: 1k; R_0805_2012Metric; MPN RC0805FR-071KL
R2: 100R_0.1%; R_1206_3216Metric; MPN RR1220P-101-D
R4: 30k_0.1%; R_0805_2012Metric; MPN ERA-6AEB303V
R5: 10k_0.1%; R_0805_2012Metric; MPN ERA-6AEB103V
R6, R7: 4.7k; R_0805_2012Metric; MPN RC0805FR-074K7L
R8, R9, R15, R18: 10k; R_0805_2012Metric; MPN RC0805FR-0710KL
R11: 120R_1%; R_0805_2012Metric; MPN RC0805FR-07120RL
R12, R13: 390R_0.1%; R_0805_2012Metric; MPN RC0805FR-07390RL
R14, R17: 10R; R_0805_2012Metric; MPN RC0805FR-0710RL
R16, R19: 2.2k; R_0805_2012Metric; MPN RC0805FR-072K2L
SW1: RESET; SW_SPST_PTS645; MPN PTS645SM43SMTR92LFS
SW2: BOOT; SW_SPST_PTS645; MPN PTS645SM43SMTR92LFS
U1: LM2576HVS-5.0; TO-263-5_TabPin3; MPN LM2576HVS-5.0/NOPB
U2: AMS1117-3.3; SOT-223-3_TabPin2; MPN AMS1117-3.3
U3: LMV358; SOIC-8_3.9x4.9mm_P1.27mm; MPN LMV358IDR
U4: ADS1115; MSOP-10_3x3mm_P0.5mm; MPN ADS1115IDGSR
U5: ESP32-WROOM-32; MPN ESP32-WROOM-32E-N16
U6: MAX3485EESA; SOIC-8_3.9x4.9mm_P1.27mm; MPN MAX3485EESA+
U7: UCC27524D; SOIC-8_3.9x4.9mm_P1.27mm; MPN UCC27524D
U8: TPS26610DDF; SOT-23-8; MPN TPS26610DDFR

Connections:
+3V3: C4.1, C5.1, C9.1, C10.1, C11.1, C13.1, D5.2 (C2), R1.1, R6.1, R7.1, R8.1, R9.1, R12.1, U2.2 (VOUT), U2.4 (TAB), U4.8 (VDD), U5.2 (3V3), U6.8 (VCC), U8.6 (+Vs)
+5V: C3.1, C7.1, C14.1, C15.1, L1.2, U1.4 (FEEDBACK), U2.3 (VIN), U3.8 (V+), U7.1 (ENA), U7.6 (VDD), U7.8 (ENB)
+24V: D14.1 (K), F1.1, F2.1, F3.1, J1.1
+24V_ACT1_FUSED: D8.1 (K), F2.2, J5.1, R16.1
+24V_ACT2_FUSED: D10.1 (K), F3.2, J6.1, R19.1
+24V_LOGIC_FUSED: D1.1 (K), D2.2 (A), F1.2
+24V_LOGIC_PROT: C1.1, C2.1, D2.1 (K), U1.1 (VIN)
ACT1_LED_NET: D9.2 (A), R16.2
ACT2_LED_NET: D11.2 (A), R19.2
GATE_DRV1_OUT: R14.1, U7.7 (OUTA)
GATE_DRV2_OUT: R17.1, U7.5 (OUTB)
GND: C1.2, C2.2, C3.2, C4.2, C5.2, C6.2, C7.2, C8.2, C9.2, C10.2, C11.2, C12.2, C13.2, C14.2, C15.2, D1.2 (A), D3.1 (K), D4.2 (A), D5.1 (A1), D6.1 (K), D7.3 (GND), D12.2 (A), D14.2 (A), J1.2, J2.2, J3.2, J4.3, Q1.3 (S), Q2.3 (S), R2.2, R5.2, R13.2, R15.2, R18.2, SW1.2, SW2.2, U1.3 (GND), U1.5 (ON/OFF), U2.1 (GND), U3.4 (V-), U4.1 (ADDR), U4.3 (GND), U4.6 (AIN2), U4.7 (AIN3), U5.1 (GND), U5.15 (GND), U5.38 (GND), U5.39 (GND), U6.5 (GND), U7.3 (GND), U8.1 (GND), U8.2 (MODE), U8.3 (-Vs)
I2C_SCL: R7.2, U4.10 (SCL), U5.36 (IO22)
I2C_SDA: R6.2, U4.9 (SDA), U5.33 (IO21)
LOOP_POS: J2.1, U8.4 (IN)
LOOP_PROT: D4.1 (K), R2.1, R3.1, U8.5 (OUT)
MCU_ACT1_PWM: R15.1, U5.13 (IO14), U7.2 (INA)
MCU_ACT2_PWM: R18.1, U5.16 (IO13), U7.4 (INB)
MCU_BOOT: R9.2, SW2.1, U5.25 (IO0)
MCU_EN: C12.1, R8.2, SW1.1, U5.3 (EN)
MCU_STATUS_LED: R10.1, U5.24 (IO4)
MOSFET1_DRAIN: D8.2 (A), D9.1 (K), J5.2, Q1.2 (D)
MOSFET1_GATE: Q1.1 (G), R14.2
MOSFET2_DRAIN: D10.2 (A), D11.1 (K), J6.2, Q2.2 (D)
MOSFET2_GATE: Q2.1 (G), R17.2
PWR_LED_NET: D3.2 (A), R1.2
RS485_A: D7.1 (A), J4.1, R11.1, R12.2, U6.6 (A)
RS485_B: D7.2 (B), J4.2, JP1.2, R13.1, U6.7 (B)
RS485_DE: U5.29 (IO5), U6.2 (~RE), U6.3 (DE)
RS485_DI: U5.28 (IO17), U6.4 (DI)
RS485_RO: U5.27 (IO16), U6.1 (RO)
STATUS_LED_NET: D6.2 (A), R10.2
SW_NODE: D12.1 (K), L1.1, U1.2 (OUTPUT)
TERM_JUMP_NET: JP1.1, R11.2
V_0_10V_BUF: U3.6 (INB-), U3.7 (OUTB), U4.5 (AIN1)
V_0_10V_DIV: C8.1, D5.3 (C1_A2), R4.2, R5.1, U3.5 (INB+)
V_0_10V_IN: J3.1, R4.1
V_4_20MA_BUF: U3.1 (OUTA), U3.2 (INA-), U4.4 (AIN0)
V_SHUNT_FILT: C6.1, R3.2, U3.3 (INA+)
